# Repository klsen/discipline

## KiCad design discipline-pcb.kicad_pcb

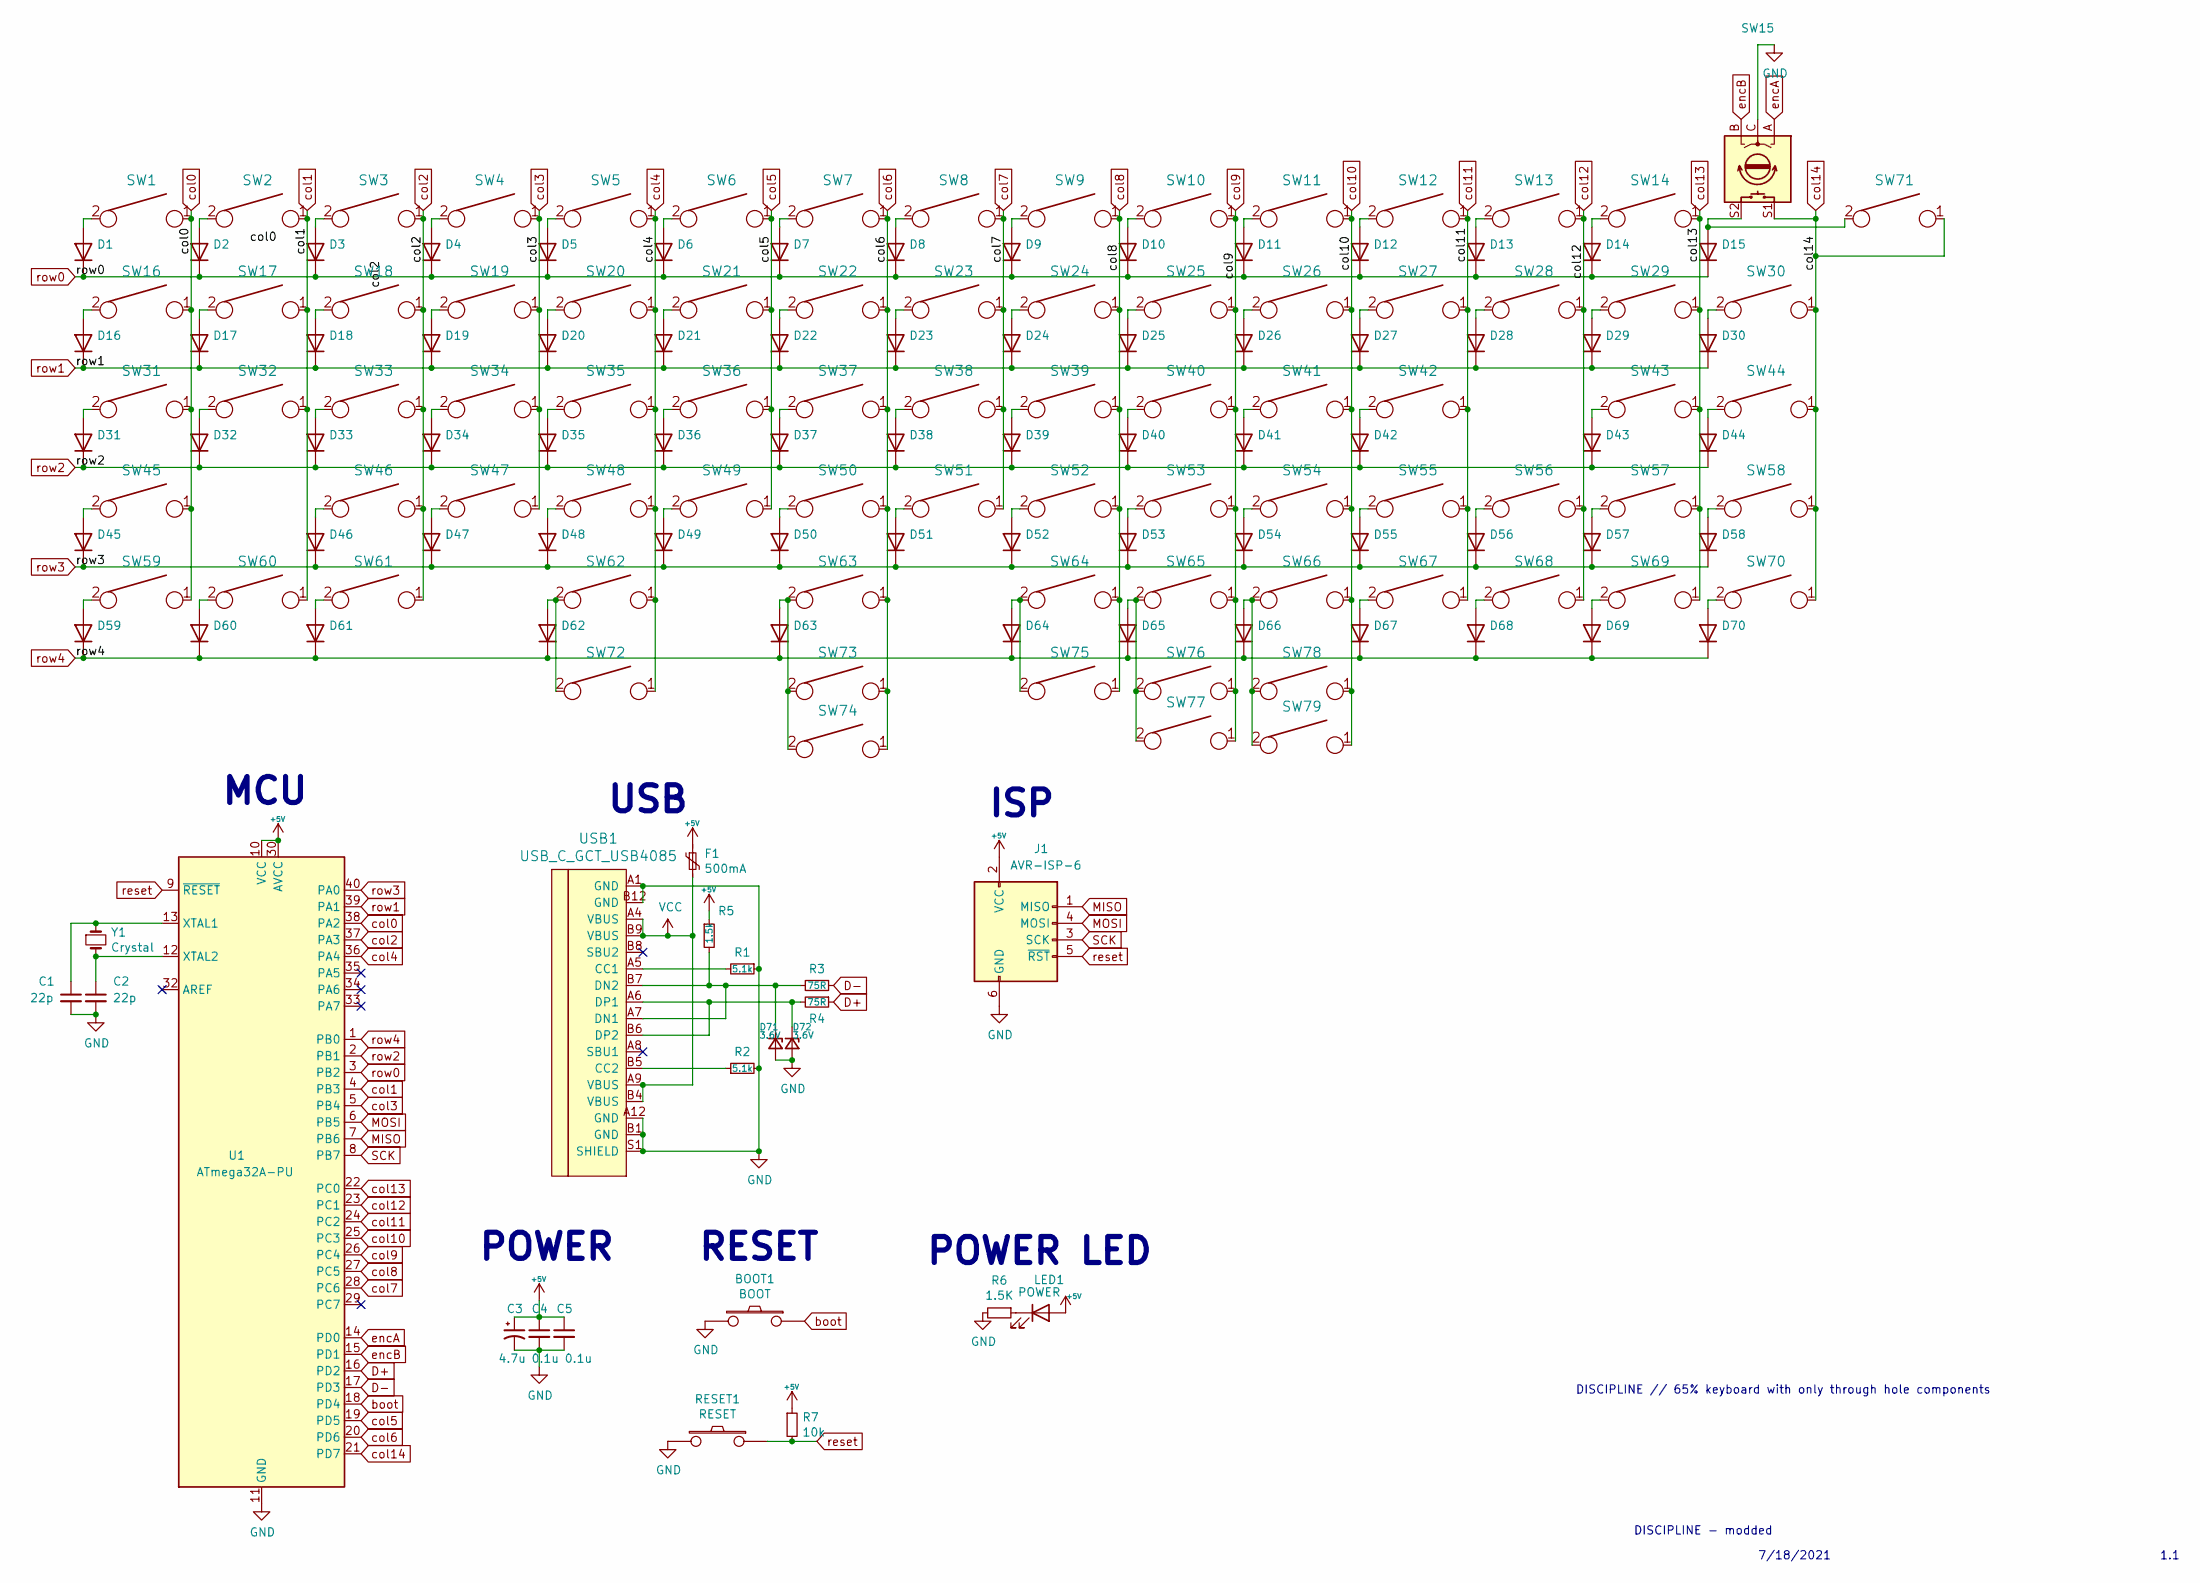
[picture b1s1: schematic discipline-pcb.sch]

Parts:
BOOT1: BOOT; SW_Tactile_SPST_Angled_PTS645Vx31-2LFS
C1, C2: 22p; C_Disc_D3.0mm_W1.6mm_P2.50mm
C3: 4.7u; CP_Radial_D4.0mm_P1.50mm
C4, C5: 0.1u; C_Disc_D4.3mm_W1.9mm_P5.00mm
D1, D2, D3, D4, D5, D6, D7, D8, D9, D10, D11, D12, D13, D14, D15, D16, D17, D18, D19, D20, D21, D22, D23, D24, D25, D26, D27, D28, D29, D30, D31, D32, D33, D34, D35, D36, D37, D38, D39, D40, D41, D42, D43, D44, D45, D46, D47, D48, D49, D50, D51, D52, D53, D54, D55, D56, D57, D58, D59, D60, D61, D62, D63, D64, D65, D66, D67, D68, D69, D70: D_DO-35_SOD27_P5.08mm_Horizontal
D71, D72: 3.6V; D_DO-35_SOD27_P5.08mm_Horizontal
F1: 500mA; polyfuse_5.1mm
J1: AVR-ISP-6; AVR_ICSP_3x2
LED1: POWER; LED_D3.0mm
R1, R2: 5.1k; R_Axial_DIN0204_L3.6mm_D1.6mm_P5.08mm_Horizontal
R3, R4: 75R; R_Axial_DIN0204_L3.6mm_D1.6mm_P5.08mm_Horizontal
R5: 1.5k; R_Axial_DIN0204_L3.6mm_D1.6mm_P5.08mm_Horizontal
R6: 1.5K; R_Axial_DIN0204_L3.6mm_D1.6mm_P5.08mm_Horizontal
R7: 10k; R_Axial_DIN0204_L3.6mm_D1.6mm_P5.08mm_Horizontal
RESET1: RESET; SW_Tactile_SPST_Angled_PTS645Vx31-2LFS
SW1, SW2, SW3, SW4, SW5, SW6, SW7, SW8, SW9, SW10, SW11, SW12, SW13, SW17, SW18, SW19, SW20, SW21, SW22, SW23, SW24, SW25, SW26, SW27, SW28, SW30, SW32, SW33, SW34, SW35, SW36, SW37, SW38, SW39, SW40, SW41, SW42, SW44, SW46, SW47, SW48, SW49, SW50, SW51, SW52, SW53, SW54, SW55, SW57, SW58, SW66, SW67, SW68, SW69, SW70, SW71: KEYSW; SW_Cherry_MX1A_1.00u_PCB-NOSCREEN
SW14: KEYSW; SW_Cherry_MX1A_2.00u_PCBNOSCREEN
SW15: Rotary_Encoder_Switch; RotaryEncoder_Alps_EC11E-Switch_Vertical_H20mm_nosilk
SW16, SW29: KEYSW; SW_Cherry_MX1A_1.50u_PCBNOSCREEN
SW31, SW56: KEYSW; SW_Cherry_MX1A_1.75u_PCBNOSCREEN
SW43, SW45: KEYSW; SW_Cherry_MX1A_2.25u_PCBNOSCREEN
SW59, SW60, SW61, SW63, SW73: KEYSW; SW_Cherry_MX1A_1.25u_PCBNOSCREEN
SW62, SW75: KEYSW; SW_Cherry_MX_2.75u_PCB_nosilk_flippedstabs
SW64, SW72: KEYSW; SW_Cherry_MX_2.25u_PCB_nosilk_fliippedstabs
SW65: KEYSW-keyboard_parts; SW_Cherry_MX1A_1.00u_PCB-NOSCREEN
SW74: KEYSW; SW_Cherry_MX_6.25u_PCB_nosilk_flippedstabs
SW76, SW78: KEYSW-keyboard_parts; SW_Cherry_MX1A_1.25u_PCBNOSCREEN
SW77, SW79: KEYSW-keyboard_parts; SW_Cherry_MX1A_1.50u_PCBNOSCREEN
U1: ATmega32A-PU; DIP-40_W15.24mm
USB1: USB_C_GCT_USB4085
Y1: Crystal; Crystal_HC49-4H_Vertical

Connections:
+5V: C3.1, C4.1, C5.1, F1.1, J1.2 (VCC), LED1.2 (A), R5.1, R7.1, U1.10 (VCC), U1.30 (AVCC)
D+: R4.1, U1.16 (PD2)
D-: R3.1, U1.17 (PD3)
GND: BOOT1.1, C1.2, C2.2, C3.2, C4.2, C5.2, D71.2 (A), D72.2 (A), J1.6 (GND), R1.1, R2.2, R6.2, RESET1.1, SW15.C, U1.11 (GND), U1.31 (GND), USB1.A1 (GND), USB1.A12 (GND), USB1.B1 (GND), USB1.B12 (GND), USB1.S1 (SHIELD)
MISO: J1.1 (MISO), U1.7 (PB6)
MOSI: J1.4 (MOSI), U1.6 (PB5)
unnamed: C1.1, U1.13 (XTAL1), Y1.1
unnamed: C2.1, U1.12 (XTAL2), Y1.2
unnamed: D1.2 (A), SW1.2
unnamed: D2.2 (A), SW2.2
unnamed: D3.2 (A), SW3.2
unnamed: D4.2 (A), SW4.2
unnamed: D5.2 (A), SW5.2
unnamed: D6.2 (A), SW6.2
unnamed: D7.2 (A), SW7.2
unnamed: D8.2 (A), SW8.2
unnamed: D9.2 (A), SW9.2
unnamed: D10.2 (A), SW10.2
unnamed: D11.2 (A), SW11.2
unnamed: D12.2 (A), SW12.2
unnamed: D13.2 (A), SW13.2
unnamed: D14.2 (A), SW14.2
unnamed: D15.2 (A), SW15.S2, SW71.2
unnamed: D16.2 (A), SW16.2
unnamed: D17.2 (A), SW17.2
unnamed: D18.2 (A), SW18.2
unnamed: D19.2 (A), SW19.2
unnamed: D20.2 (A), SW20.2
unnamed: D21.2 (A), SW21.2
unnamed: D22.2 (A), SW22.2
unnamed: D23.2 (A), SW23.2
unnamed: D24.2 (A), SW24.2
unnamed: D25.2 (A), SW25.2
unnamed: D26.2 (A), SW26.2
unnamed: D27.2 (A), SW27.2
unnamed: D28.2 (A), SW28.2
unnamed: D29.2 (A), SW29.2
unnamed: D30.2 (A), SW30.2
unnamed: D31.2 (A), SW31.2
unnamed: D32.2 (A), SW32.2
unnamed: D33.2 (A), SW33.2
unnamed: D34.2 (A), SW34.2
unnamed: D35.2 (A), SW35.2
unnamed: D36.2 (A), SW36.2
unnamed: D37.2 (A), SW37.2
unnamed: D38.2 (A), SW38.2
unnamed: D39.2 (A), SW39.2
unnamed: D40.2 (A), SW40.2
unnamed: D41.2 (A), SW41.2
unnamed: D42.2 (A), SW42.2
unnamed: D43.2 (A), SW43.2
unnamed: D44.2 (A), SW44.2
unnamed: D45.2 (A), SW45.2
unnamed: D46.2 (A), SW46.2
unnamed: D47.2 (A), SW47.2
unnamed: D48.2 (A), SW48.2
unnamed: D49.2 (A), SW49.2
unnamed: D50.2 (A), SW50.2
unnamed: D51.2 (A), SW51.2
unnamed: D52.2 (A), SW52.2
unnamed: D53.2 (A), SW53.2
unnamed: D54.2 (A), SW54.2
unnamed: D55.2 (A), SW55.2
unnamed: D56.2 (A), SW56.2
unnamed: D57.2 (A), SW57.2
unnamed: D58.2 (A), SW58.2
unnamed: D59.2 (A), SW59.2
unnamed: D60.2 (A), SW60.2
unnamed: D61.2 (A), SW61.2
unnamed: D62.2 (A), SW62.2, SW72.2
unnamed: D63.2 (A), SW63.2, SW73.2, SW74.2
unnamed: D64.2 (A), SW64.2, SW75.2
unnamed: D65.2 (A), SW65.2, SW76.2, SW77.2
unnamed: D66.2 (A), SW66.2, SW78.2, SW79.2
unnamed: D67.2 (A), SW67.2
unnamed: D68.2 (A), SW68.2
unnamed: D69.2 (A), SW69.2
unnamed: D70.2 (A), SW70.2
unnamed: D71.1 (K), R3.2, R5.2, USB1.A7 (DN1), USB1.B7 (DN2)
unnamed: D72.1 (K), R4.2, USB1.A6 (DP1), USB1.B6 (DP2)
unnamed: LED1.1 (K), R6.1
unnamed: R1.2, USB1.A5 (CC1)
unnamed: R2.1, USB1.B5 (CC2)
SCK: J1.3 (SCK), U1.8 (PB7)
VCC: F1.2, USB1.A4 (VBUS), USB1.A9 (VBUS), USB1.B4 (VBUS), USB1.B9 (VBUS)
boot: BOOT1.2, U1.18 (PD4)
col0: SW1.1, SW16.1, SW31.1, SW45.1, SW59.1, U1.38 (PA2)
col1: SW2.1, SW17.1, SW32.1, SW60.1, U1.4 (PB3)
col2: SW3.1, SW18.1, SW33.1, SW46.1, SW61.1, U1.37 (PA3)
col3: SW4.1, SW19.1, SW34.1, SW47.1, U1.5 (PB4)
col4: SW5.1, SW20.1, SW35.1, SW48.1, SW62.1, SW72.1, U1.36 (PA4)
col5: SW6.1, SW21.1, SW36.1, SW49.1, U1.19 (PD5)
col6: SW7.1, SW22.1, SW37.1, SW50.1, SW63.1, SW73.1, SW74.1, U1.20 (PD6)
col7: SW8.1, SW23.1, SW38.1, SW51.1, U1.28 (PC6)
col8: SW9.1, SW24.1, SW39.1, SW52.1, SW64.1, SW75.1, U1.27 (PC5)
col9: SW10.1, SW25.1, SW40.1, SW53.1, SW65.1, SW76.1, SW77.1, U1.26 (PC4)
col10: SW11.1, SW26.1, SW41.1, SW54.1, SW66.1, SW78.1, SW79.1, U1.25 (PC3)
col11: SW12.1, SW27.1, SW42.1, SW55.1, SW67.1, U1.24 (PC2)
col12: SW13.1, SW28.1, SW56.1, SW68.1, U1.23 (PC1)
col13: SW14.1, SW29.1, SW43.1, SW57.1, SW69.1, U1.22 (PC0)
col14: SW15.S1, SW30.1, SW44.1, SW58.1, SW70.1, SW71.1, U1.21 (PD7)
encA: SW15.A, U1.14 (PD0)
encB: SW15.B, U1.15 (PD1)
reset: J1.5 (~RST), R7.2, RESET1.2, U1.9 (~RESET)
row0: D1.1 (K), D2.1 (K), D3.1 (K), D4.1 (K), D5.1 (K), D6.1 (K), D7.1 (K), D8.1 (K), D9.1 (K), D10.1 (K), D11.1 (K), D12.1 (K), D13.1 (K), D14.1 (K), D15.1 (K), U1.3 (PB2)
row1: D16.1 (K), D17.1 (K), D18.1 (K), D19.1 (K), D20.1 (K), D21.1 (K), D22.1 (K), D23.1 (K), D24.1 (K), D25.1 (K), D26.1 (K), D27.1 (K), D28.1 (K), D29.1 (K), D30.1 (K), U1.39 (PA1)
row2: D31.1 (K), D32.1 (K), D33.1 (K), D34.1 (K), D35.1 (K), D36.1 (K), D37.1 (K), D38.1 (K), D39.1 (K), D40.1 (K), D41.1 (K), D42.1 (K), D43.1 (K), D44.1 (K), U1.2 (PB1)
row3: D45.1 (K), D46.1 (K), D47.1 (K), D48.1 (K), D49.1 (K), D50.1 (K), D51.1 (K), D52.1 (K), D53.1 (K), D54.1 (K), D55.1 (K), D56.1 (K), D57.1 (K), D58.1 (K), U1.40 (PA0)
row4: D59.1 (K), D60.1 (K), D61.1 (K), D62.1 (K), D63.1 (K), D64.1 (K), D65.1 (K), D66.1 (K), D67.1 (K), D68.1 (K), D69.1 (K), D70.1 (K), U1.1 (PB0)

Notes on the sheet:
DISCIPLINE // 65% keyboard with only through hole components
7/18/2021
DISCIPLINE - modded
1.1
MCU
USB
ISP
POWER
RESET
POWER LED

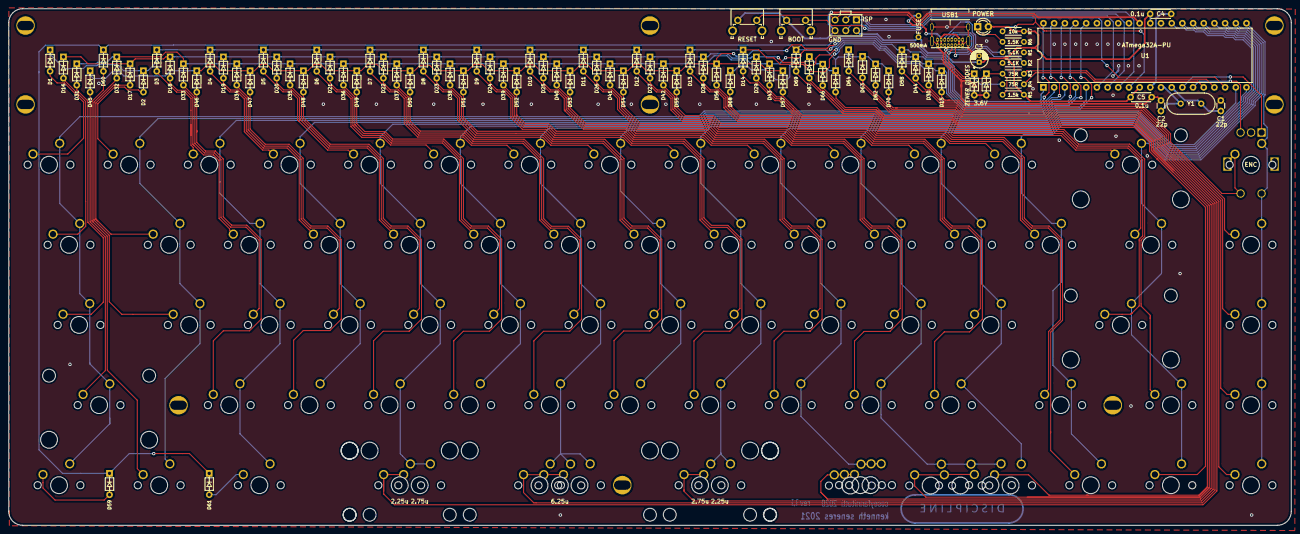
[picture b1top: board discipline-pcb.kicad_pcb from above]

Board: 2 copper layers, 304.9 x 122.8 mm, 171 parts (0 on the bottom side), 109 nets.

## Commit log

2021-07-18 modified schematic and footprints for my layout. still need to rearrange traces
2021-07-18 little footprint changes in schematic
2021-07-18 traces for matrix columns done
2021-07-18 pre drc
2021-07-19 pcb done
2021-07-20 moved mounting holes
2021-07-20 big plate energy
2021-07-20 turned the rotary encoder slot into a switch/encoder combo slot
2021-07-24 almost sent a pcb with a hole through a trace there
2021-07-24 gerber files
2021-07-24 stl files of 3d models for case and encoder knob
2021-07-25 maybe moved holes idk
2021-07-25 split body in half with dovetails, changed height to fix problem, adjusted holes
2021-07-25 adjusted model for EN11 encoder shaft
2021-07-25 something to practice putting threaded inserts on without ruining the case
2021-07-25 file changes
2021-07-26 changed pcb mounting holes to be oval shaped for better odds of aligning with case. updated gerbers
2021-07-26 oops forgot the zip
2021-07-27 removed silk on encoder footprint. updated gerbers
2021-09-30 updated 3d printed parts
2021-09-30 new plate version with bigger hole for encoder for hotswapping
2021-10-02 added 3x1u and 2x1.5u options in bottom right modifier section. renumbered switches and diodes
2021-10-02 replaced reset and boot buttons with right angle buttons
2021-10-02 change to fix fills
2021-10-02 plate for 3x1u option
2021-10-02 reducing number of screws and changing placements
2021-10-04 enlarged encoder mounting holes for compatibility with mill-max sockets
